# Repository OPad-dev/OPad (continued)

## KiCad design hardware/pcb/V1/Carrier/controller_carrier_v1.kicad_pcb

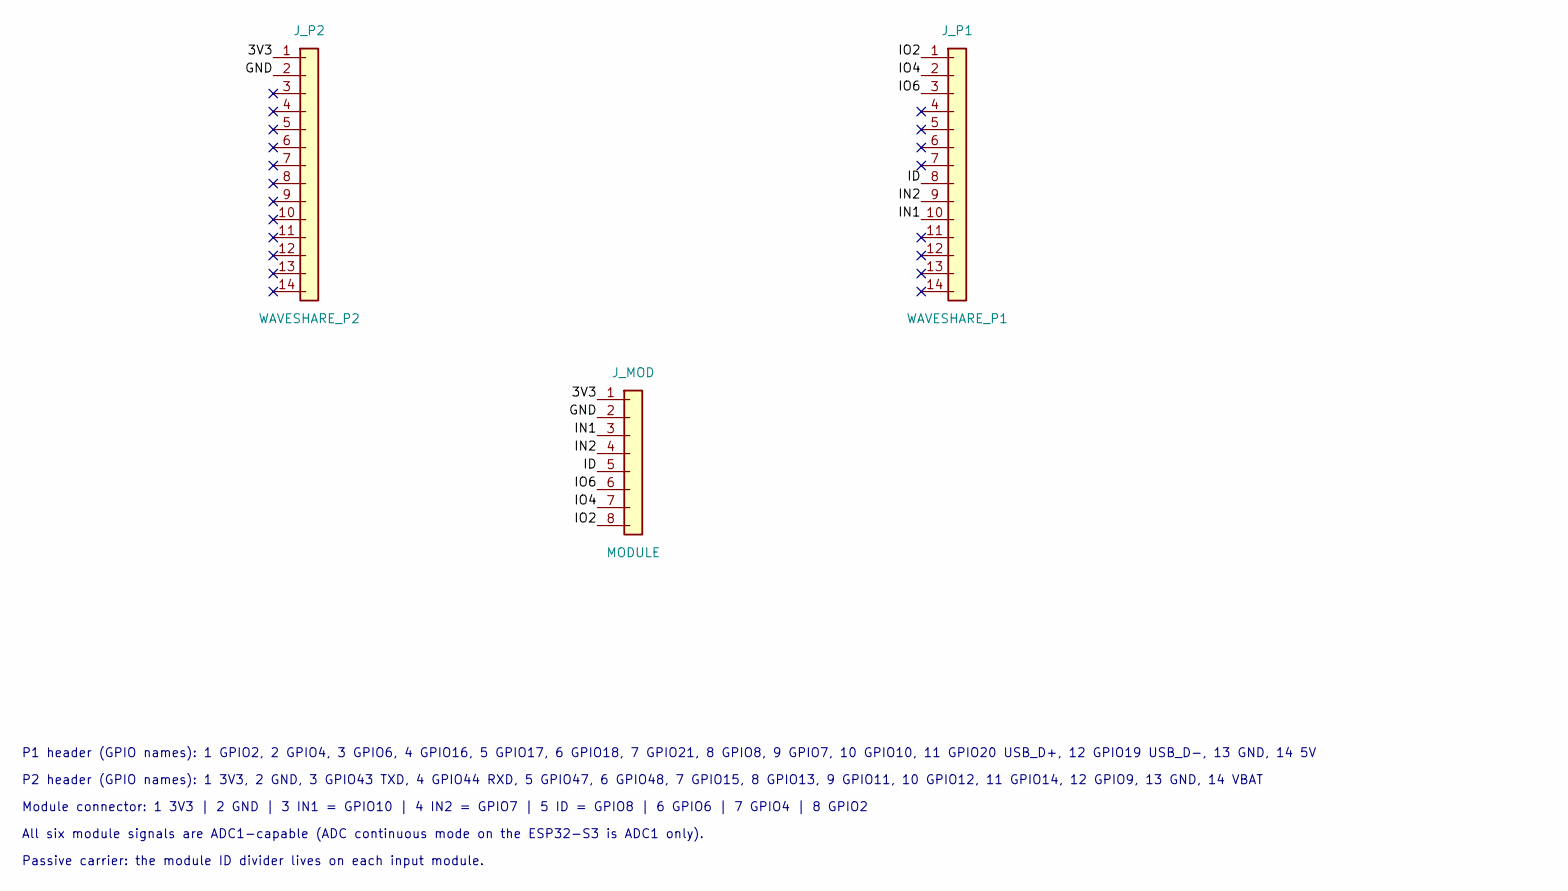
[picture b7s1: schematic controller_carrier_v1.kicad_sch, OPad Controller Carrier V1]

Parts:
J_MOD: MODULE; JST_SH_SM08B-SRSS-TB_1x08-1MP_P1.00mm_Horizontal; MPN JST SM08B-SRSS-TB(LF)(SN); LCSC C160407
J_P1: WAVESHARE_P1; PinSocket_1x14_P2.54mm_Vertical; MPN HCTL PM254-1-14-Z-8.5; LCSC C2897377
J_P2: WAVESHARE_P2; PinSocket_1x14_P2.54mm_Vertical; MPN HCTL PM254-1-14-Z-8.5; LCSC C2897377

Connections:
/3V3: J_MOD.1, J_P2.1
/GND: J_MOD.2, J_P2.2
/ID: J_MOD.5, J_P1.8
/IN1: J_MOD.3, J_P1.10
/IN2: J_MOD.4, J_P1.9
/IO2: J_MOD.8, J_P1.1
/IO4: J_MOD.7, J_P1.2
/IO6: J_MOD.6, J_P1.3

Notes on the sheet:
P1 header (GPIO names): 1 GPIO2, 2 GPIO4, 3 GPIO6, 4 GPIO16, 5 GPIO17, 6 GPIO18, 7 GPIO21, 8 GPIO8, 9 GPIO7, 10 GPIO10, 11 GPIO20 USB_D+, 12 GPIO19 USB_D-, 13 GND, 14 5V
P2 header (GPIO names): 1 3V3, 2 GND, 3 GPIO43 TXD, 4 GPIO44 RXD, 5 GPIO47, 6 GPIO48, 7 GPIO15, 8 GPIO13, 9 GPIO11, 10 GPIO12, 11 GPIO14, 12 GPIO9, 13 GND, 14 VBAT
Module connector: 1 3V3 | 2 GND | 3 IN1 = GPIO10 | 4 IN2 = GPIO7 | 5 ID = GPIO8 | 6 GPIO6 | 7 GPIO4 | 8 GPIO2
All six module signals are ADC1-capable (ADC continuous mode on the ESP32-S3 is ADC1 only).
Passive carrier: the module ID divider lives on each input module.

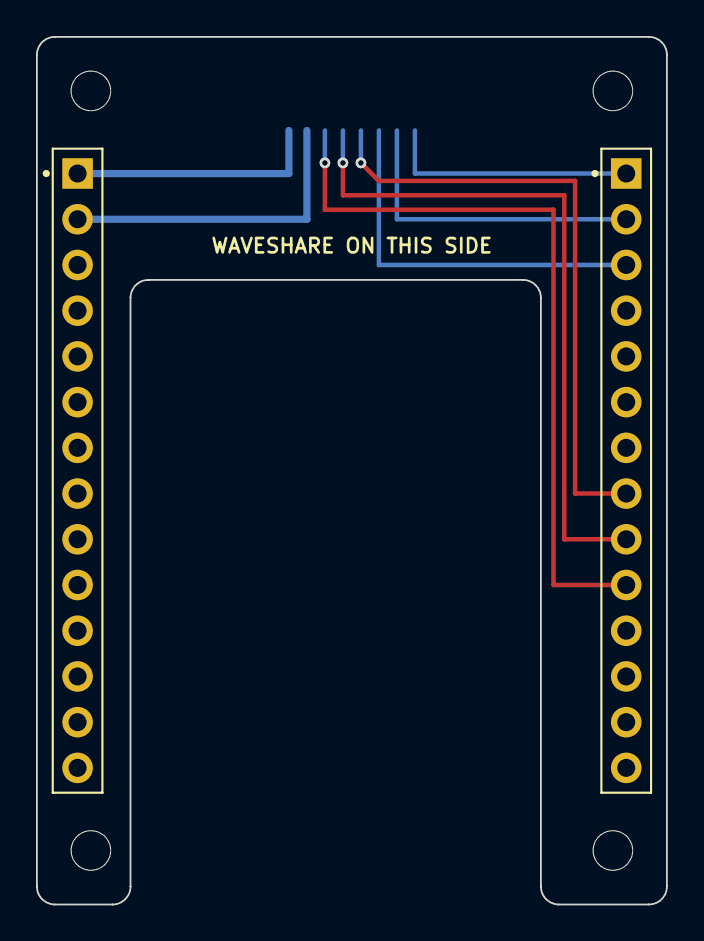
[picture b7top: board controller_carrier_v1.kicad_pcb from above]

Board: 2 copper layers, 35.0 x 48.2 mm, 7 parts (1 on the bottom side), 8 nets.

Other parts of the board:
H1, H2, H3, H4: MountingHole_2.2mm_M2

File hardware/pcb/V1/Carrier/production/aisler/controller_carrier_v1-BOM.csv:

Reference,Quantity,Value,Footprint,MFG,MPN,LCSC,Side,Type
"J_P2",1,WAVESHARE_P2,PinSocket_1x14_P2.54mm_Vertical,HCTL,PM254-1-14-Z-8.5,C2897377,top,THT
"J_P1",1,WAVESHARE_P1,PinSocket_1x14_P2.54mm_Vertical,HCTL,PM254-1-14-Z-8.5,C2897377,top,THT
"J_MOD",1,MODULE,JST_SH_SM08B-SRSS-TB_1x08-1MP_P1.00mm_Horizontal,JST,SM08B-SRSS-TB(LF)(SN),C160407,bottom,SMD

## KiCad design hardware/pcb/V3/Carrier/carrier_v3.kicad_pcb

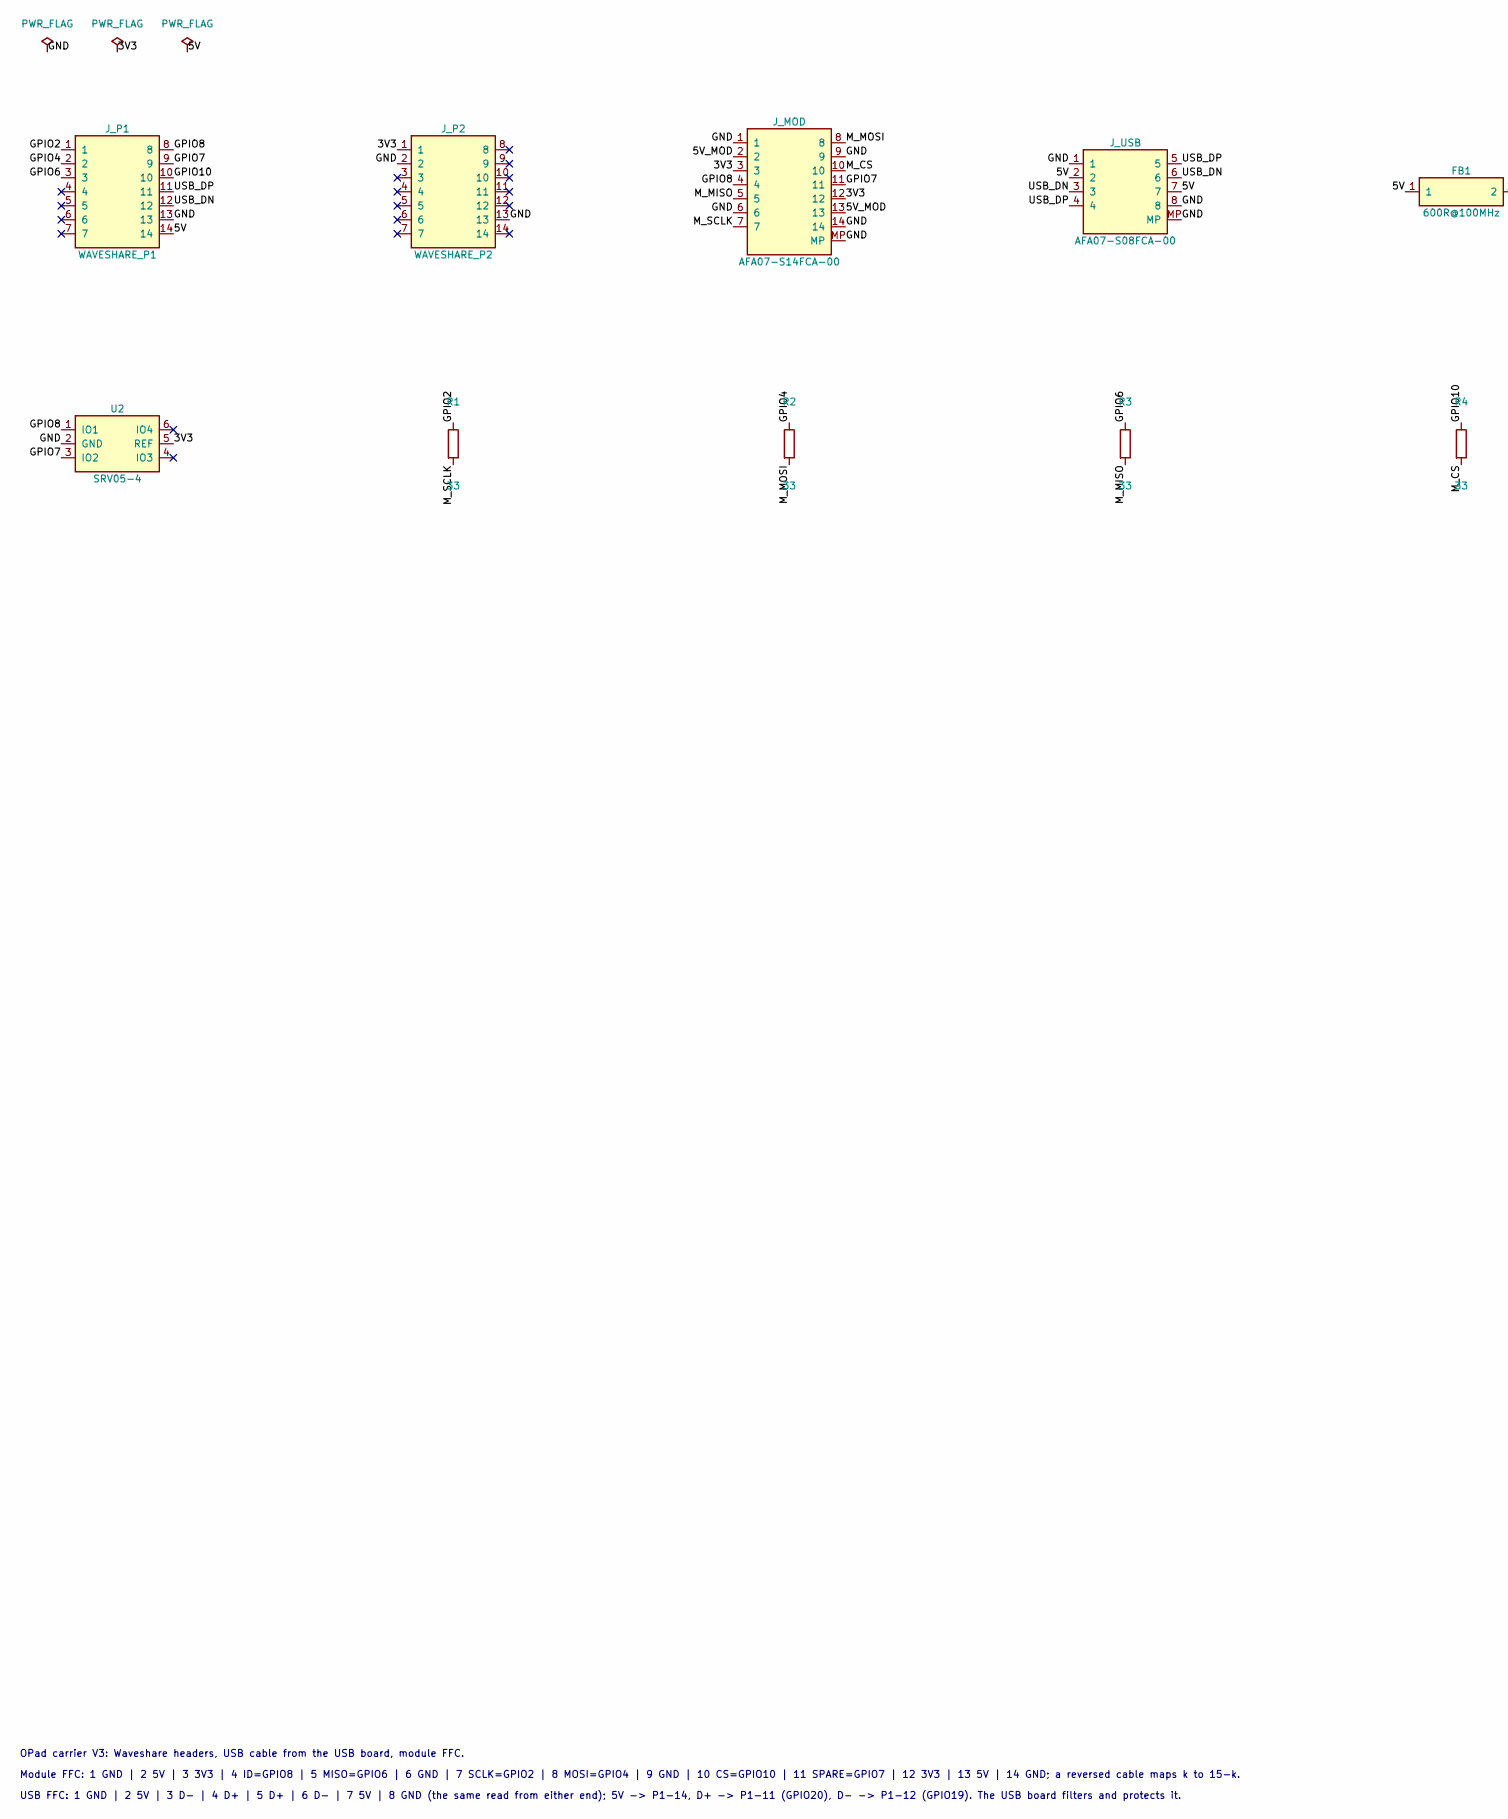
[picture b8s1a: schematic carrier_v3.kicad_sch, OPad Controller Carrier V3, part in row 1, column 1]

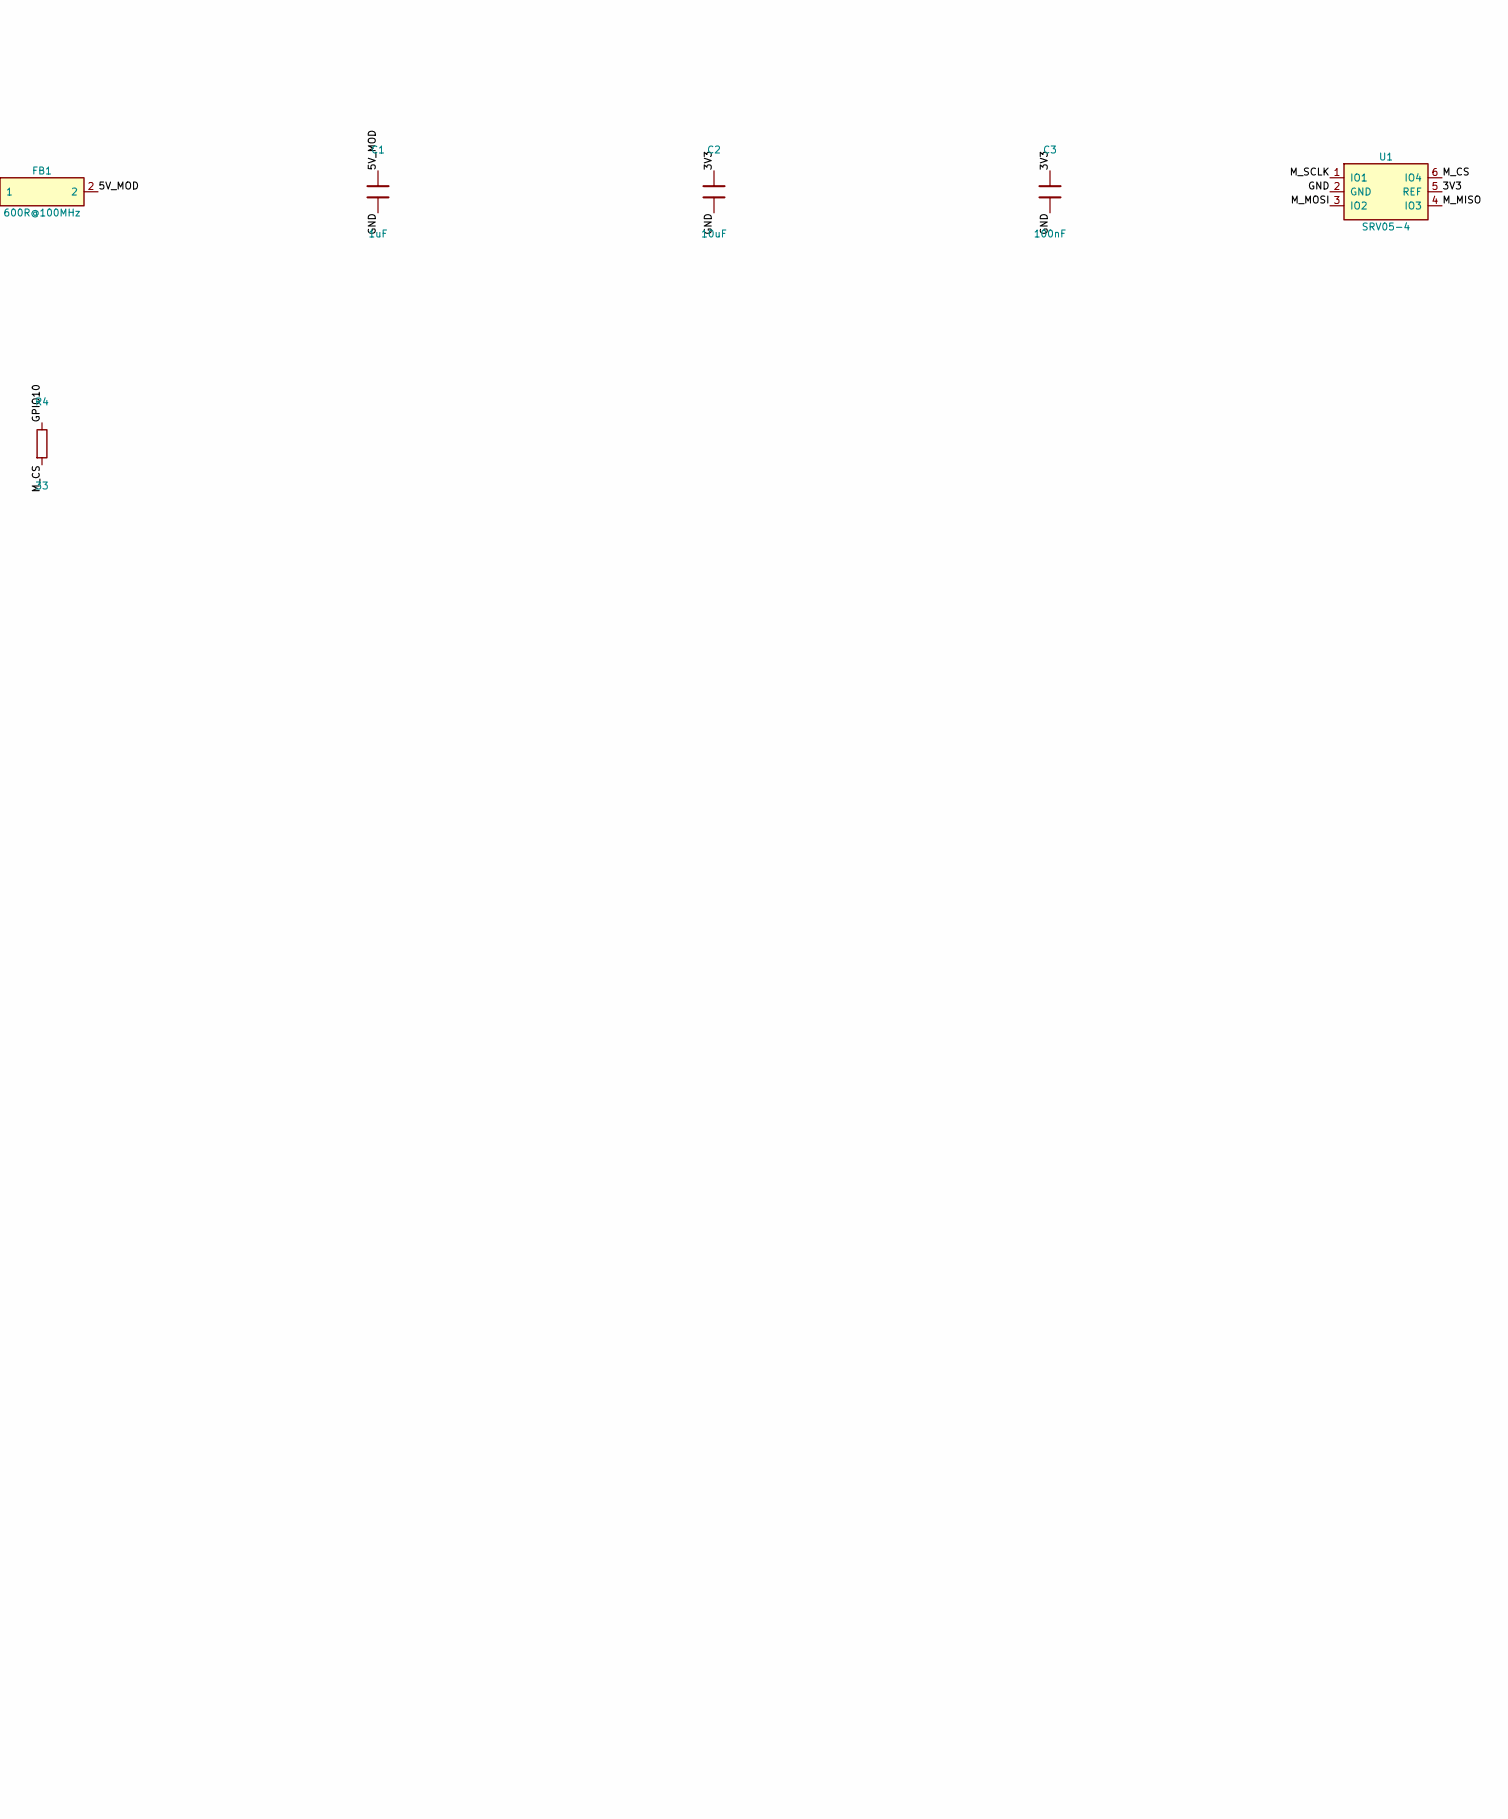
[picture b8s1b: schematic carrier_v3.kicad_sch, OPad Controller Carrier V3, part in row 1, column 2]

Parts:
C1: 1uF; C_0603_1608Metric; MPN Samsung CL10A105KB8NNNC; LCSC C15849
C2: 10uF; C_0603_1608Metric; MPN Samsung CL10A106KP8NNNC; LCSC C19702
C3: 100nF; C_0603_1608Metric; MPN YAGEO CC0603KRX7R9BB104; LCSC C14663
FB1: 600R@100MHz; L_0603_1608Metric; MPN TDK MPZ1608S601ATA00; LCSC C107335
J_MOD: AFA07-S14FCA-00; FFC_JUSHUO_AFA07-S14FCA_1x14-1MP_P1.0mm_Horizontal; MPN JUSHUO AFA07-S14FCA-00; LCSC C262720
J_P1: WAVESHARE_P1; PinSocket_1x14_P2.54mm_Vertical; MPN XUNPU FH2.54-09-14PZD; LCSC C7500781
J_P2: WAVESHARE_P2; PinSocket_1x14_P2.54mm_Vertical; MPN XUNPU FH2.54-09-14PZD; LCSC C7500781
J_USB: AFA07-S08FCA-00; FFC_JUSHUO_AFA07-S08FCA_1x08-1MP_P1.0mm_Horizontal; MPN JUSHUO AFA07-S08FCA-00; LCSC C262714
R1, R2, R3, R4: 33; R_0603_1608Metric; MPN UNI-ROYAL 0603WAF330JT5E; LCSC C23140
U1, U2: SRV05-4; SOT-23-6; MPN ProTek SRV05-4-P-T7; LCSC C85364

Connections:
/3V3: C2.1, C3.1, J_MOD.3, J_MOD.12, J_P2.1, U1.5 (REF), U2.5 (REF)
/5V: FB1.1, J_P1.14, J_USB.2, J_USB.7
/5V_MOD: C1.1, FB1.2, J_MOD.2, J_MOD.13
/GND: C1.2, C2.2, C3.2, J_MOD.1, J_MOD.6, J_MOD.9, J_MOD.14, J_MOD.MP, J_P1.13, J_P2.2, J_P2.13, J_USB.1, J_USB.8, J_USB.MP, U1.2 (GND), U2.2 (GND)
/GPIO2: J_P1.1, R1.1
/GPIO4: J_P1.2, R2.1
/GPIO6: J_P1.3, R3.1
/GPIO7: J_MOD.11, J_P1.9, U2.3 (IO2)
/GPIO8: J_MOD.4, J_P1.8, U2.1 (IO1)
/GPIO10: J_P1.10, R4.1
/M_CS: J_MOD.10, R4.2, U1.6 (IO4)
/M_MISO: J_MOD.5, R3.2, U1.4 (IO3)
/M_MOSI: J_MOD.8, R2.2, U1.3 (IO2)
/M_SCLK: J_MOD.7, R1.2, U1.1 (IO1)
/USB_DN: J_P1.12, J_USB.3, J_USB.6
/USB_DP: J_P1.11, J_USB.4, J_USB.5

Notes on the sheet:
OPad carrier V3: Waveshare headers, USB cable from the USB board, module FFC.
Module FFC: 1 GND | 2 5V | 3 3V3 | 4 ID=GPIO8 | 5 MISO=GPIO6 | 6 GND | 7 SCLK=GPIO2 | 8 MOSI=GPIO4 | 9 GND | 10 CS=GPIO10 | 11 SPARE=GPIO7 | 12 3V3 | 13 5V | 14 GND; a reversed cable maps k to 15-k.
USB FFC: 1 GND | 2 5V | 3 D- | 4 D+ | 5 D+ | 6 D- | 7 5V | 8 GND (the same read from either end); 5V -> P1-14, D+ -> P1-11 (GPIO20), D- -> P1-12 (GPIO19). The USB board filters and protects it.

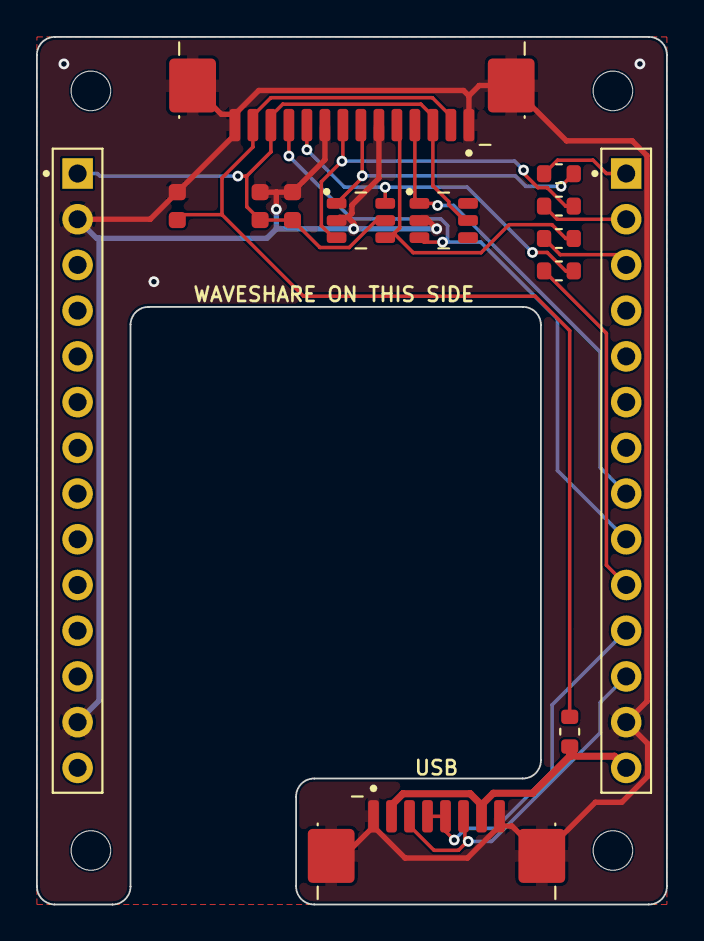
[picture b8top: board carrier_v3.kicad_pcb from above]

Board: 2 copper layers, 35.0 x 48.2 mm, 18 parts (0 on the bottom side), 16 nets.

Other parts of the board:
H1, H2, H3, H4: MountingHole_2.2mm_M2

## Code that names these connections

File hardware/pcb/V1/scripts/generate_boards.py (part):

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MODULE_PINOUT = {
    "1": "3V3",
    "2": "GND",
    "3": "IN1",    # GPIO10  KEY1 (MX)  / analog 1 (Hall)
    "4": "IN2",    # GPIO7   KEY2 (MX)  / analog 2 (Hall)
    "5": "ID",     # GPIO8   module ID voltage divider (ADC)
    "6": "IO6",    # GPIO6   spare, e.g. SPI MISO
    "7": "IO4",    # GPIO4   spare, e.g. SPI MOSI / CS
    "8": "IO2",    # GPIO2   spare, e.g. SPI SCK
}

JST = dict(symbol="Conn_01x08", footprint="JST_SH_SM08B-SRSS-TB_1x08-1MP_P1.00mm_Horizontal",
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
    write_schematic(directory, project, "OPad MX Input Module V1", parts, [
        "Module connector pinout (same on every input module):",
        "1 3V3 | 2 GND | 3 IN1 = GPIO10 | 4 IN2 = GPIO7 | 5 ID = GPIO8 | 6 GPIO6 | 7 GPIO4 | 8 GPIO2",
        "MX V1: keys switch IN1/IN2 to GND (10k pull-ups). ID = 3V3 x 10k/(100k+10k) = 0.30 V.",
        "Sockets, J1 and all passives are on the bottom side; the switches sit on top under the plate.",
    ])
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
    p1_nets = {1: "IO2", 2: "IO4", 3: "IO6", 8: "ID", 9: "IN2", 10: "IN1"}
    p2_nets = {1: "3V3", 2: "GND"}
    p1_names = ["GPIO2", "GPIO4", "GPIO6", "GPIO16", "GPIO17", "GPIO18", "GPIO21", "GPIO8", "GPIO7",
                "GPIO10", "GPIO20 USB_D+", "GPIO19 USB_D-", "GND", "5V"]
    p2_names = ["3V3", "GND", "GPIO43 TXD", "GPIO44 RXD", "GPIO47", "GPIO48", "GPIO15", "GPIO13",
                "GPIO11", "GPIO12", "GPIO14", "GPIO9", "GND", "VBAT"]

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
    notes = ["P1 header (GPIO names): " + ", ".join("%d %s" % (i + 1, n) for i, n in enumerate(p1_names)),
             "P2 header (GPIO names): " + ", ".join("%d %s" % (i + 1, n) for i, n in enumerate(p2_names)),
             "Module connector: 1 3V3 | 2 GND | 3 IN1 = GPIO10 | 4 IN2 = GPIO7 | 5 ID = GPIO8 | 6 GPIO6 | 7 GPIO4 | 8 GPIO2",
             "All six module signals are ADC1-capable (ADC continuous mode on the ESP32-S3 is ADC1 only).",
             "Passive carrier: the module ID divider lives on each input module."]
    write_schematic(directory, project, "OPad Controller Carrier V1", parts, notes)
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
